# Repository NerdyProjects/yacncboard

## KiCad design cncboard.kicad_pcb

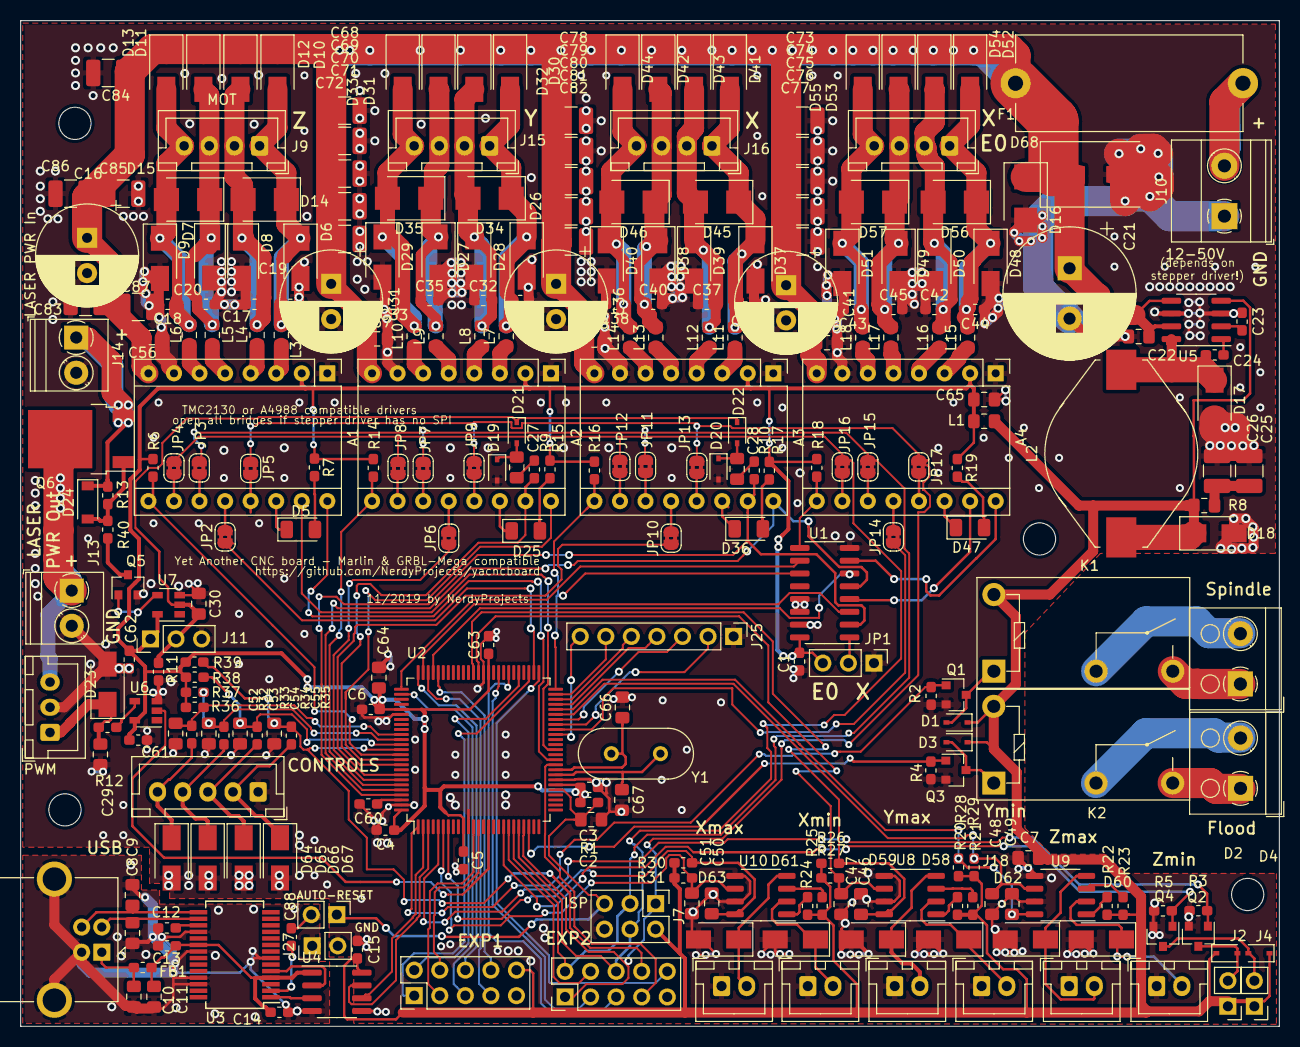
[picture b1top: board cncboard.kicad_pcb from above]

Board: 2 copper layers, 125.1 x 99.9 mm, 287 parts (0 on the bottom side), 174 nets.

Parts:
A1, A2, A3, A4: Pololu_Breakout_A4988; Pololu_Breakout-16_15.2x20.3mm
C1, C3, C4, C5, C6, C12, C13, C14, C15, C23, C24, C60, C61, C62, C63, C88: 100n; C_0603_1608Metric_Pad1.05x0.95mm_HandSolder
C2, C10: 10n; C_0805_2012Metric_Pad1.15x1.40mm_HandSolder
C7, C46, C47, C48, C49, C50, C51, C52, C53, C54, C55, C64, C65: 1µ; C_0805_2012Metric_Pad1.15x1.40mm_HandSolder
C8, C9, C66, C67: 47p; C_0805_2012Metric_Pad1.15x1.40mm_HandSolder
C11: 4u7; C_0805_2012Metric_Pad1.15x1.40mm_HandSolder
C16, C31, C36, C41: 100µF/63V; CP_Radial_D10.0mm_P3.50mm
C17, C18, C19, C20, C32, C33, C34, C35, C37, C38, C39, C40, C42, C43, C44, C45: 470p; C_0603_1608Metric_Pad1.05x0.95mm_HandSolder
C21: 470µ/63V; CP_Radial_D13.0mm_P5.00mm
C22: 1µ/50V; C_0805_2012Metric_Pad1.15x1.40mm_HandSolder
C25, C26: 22µ; C_1210_3225Metric_Pad1.42x2.65mm_HandSolder
C27, C28: 220n; C_0805_2012Metric_Pad1.15x1.40mm_HandSolder
C29: 1n; C_0805_2012Metric_Pad1.15x1.40mm_HandSolder
C30: 10µ; C_0805_2012Metric_Pad1.15x1.40mm_HandSolder
C56, C57, C58, C59: 2u2/50V; C_0805_2012Metric_Pad1.15x1.40mm_HandSolder
C68, C69, C70, C71, C72, C73, C74, C75, C76, C77, C78, C79, C80, C81, C82, C83, C84, C85, C86, C87: 10u/50V; C_1210_3225Metric_Pad1.42x2.65mm_HandSolder
D1, D2, D3, D4, D19, D20, D21, D22: 1N4148WS; D_SOD-323
D5, D25, D36, D47: LED; LED_1206_3216Metric
D6, D7, D8, D9, D10, D11, D12, D13, D17, D26, D27, D28, D29, D30, D31, D32, D33, D37, D38, D39, D40, D41, D42, D43, D44, D48, D49, D50, D51, D52, D53, D54, D55: SK36SMA; D_SMA
D14, D15, D16, D34, D35, D45, D46, D56, D57: SMBJ43CA; D_SMB
D18, D23, D58, D59, D60, D61, D62, D63, D64, D65, D66, D67: SMAJ5.0A; D_SMA
D24: MMSZ 12T1G; D_SOD-123
D68: SK36SMA; D_SMB-SMC_Universal_Handsoldering
F1: T10A; Fuseholder_Cylinder-5x20mm_Stelvio-Kontek_PTF78_Horizontal_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
FB1: BLM18PG471SN1D; L_0603_1608Metric_Pad1.05x0.95mm_HandSolder
H1, H2, H3, H4: MountingHole; MountingHole_3.2mm_M3
J1: Spindle; TerminalBlock_RND_205-00001_1x02_P5.00mm_Horizontal
J2: SPINDLE_DIRECTION; PinHeader_1x02_P2.54mm_Vertical
J3: Coolant_flood; TerminalBlock_RND_205-00001_1x02_P5.00mm_Horizontal
J4: COOLANT_MIST; PinHeader_1x02_P2.54mm_Vertical
J5: EXP1; PinHeader_2x05_P2.54mm_Vertical
J6: EXP2; PinHeader_2x05_P2.54mm_Vertical
J7: ISP; PinHeader_2x03_P2.54mm_Vertical
J8: USB_B; USB_B_OST_USB-B1HSxx_Horizontal
J9, J15, J16, J17: MOT; JST_XH_B4B-XH-A_1x04_P2.50mm_Vertical
J10: 12-45V; TerminalBlock_Phoenix_MKDS-1,5-2_1x02_P5.00mm_Horizontal
J11: Laser on/off/auto; PinHeader_1x03_P2.54mm_Vertical
J12: LASER_3PIN; JST_XH_B3B-XH-A_1x03_P2.50mm_Vertical
J13: Laser_Out; TerminalBlock_Phoenix_PT-1,5-2-3.5-H_1x02_P3.50mm_Horizontal
J14: Laser_Vcc; TerminalBlock_Phoenix_PT-1,5-2-3.5-H_1x02_P3.50mm_Horizontal
J18: Y_MIN; JST_XH_B2B-XH-A_1x02_P2.50mm_Vertical
J19: Y_MAX; JST_XH_B2B-XH-A_1x02_P2.50mm_Vertical
J20: Z_MIN; JST_XH_B2B-XH-A_1x02_P2.50mm_Vertical
J21: Z_MAX; JST_XH_B2B-XH-A_1x02_P2.50mm_Vertical
J22: X_MIN; JST_XH_B2B-XH-A_1x02_P2.50mm_Vertical
J23: X_MAX; JST_XH_B2B-XH-A_1x02_P2.50mm_Vertical
J24: Controls; JST_XH_B5B-XH-A_1x05_P2.50mm_Vertical
J25: Conn_01x07; PinHeader_1x07_P2.54mm_Vertical
J26: AUTORESET; PinHeader_1x02_P2.54mm_Vertical
J27: GND_BRIDGE; PinHeader_1x02_P2.54mm_Vertical
JP1: SolderJumper_3_Open; PinHeader_1x03_P2.54mm_Vertical
JP2, JP6, JP10, JP14: MS3; SolderJumper-2_P1.3mm_Bridged2Bar_RoundedPad1.0x1.5mm
JP3, JP7, JP11, JP15: MS2; SolderJumper-2_P1.3mm_Bridged2Bar_RoundedPad1.0x1.5mm
JP4, JP5, JP8, JP9, JP12, JP13, JP16, JP17: MS1; SolderJumper-2_P1.3mm_Bridged2Bar_RoundedPad1.0x1.5mm
K1, K2: G5Q1AEU5DC; Relay_SPST_Omron-G5Q-1A
L1: BLM18PG471SN1D; L_0805_2012Metric_Pad1.15x1.40mm_HandSolder
L2: 100µ; L_Fastron_PISR_Handsoldering
L3, L4, L5, L6, L7, L8, L9, L10, L11, L12, L13, L14, L15, L16, L17, L18: BLM21PG600; L_0805_2012Metric_Pad1.15x1.40mm_HandSolder
Q1, Q2, Q3, Q4: AO3400; SOT-23
Q5: BSS138; SOT-23
Q6: AOD409; TO-252-2
R1, R2, R3, R4, R5, R6, R14, R16, R18, R26, R27, R28, R29, R30, R31, R36, R37, R38, R39: 10k; R_0603_1608Metric_Pad1.05x0.95mm_HandSolder
R7, R11, R15, R17, R19: 1k; R_0603_1608Metric_Pad1.05x0.95mm_HandSolder
R8: 0.1; R_0805_2012Metric_Pad1.15x1.40mm_HandSolder
R9, R10, R20, R21, R22, R23, R24, R25, R32, R33, R34, R35: 470; R_0603_1608Metric_Pad1.05x0.95mm_HandSolder
R12: 100; R_0603_1608Metric_Pad1.05x0.95mm_HandSolder
R13: 100k; R_0603_1608Metric_Pad1.05x0.95mm_HandSolder
R40: 4k7; R_0603_1608Metric_Pad1.05x0.95mm_HandSolder
U1: 74LS157; SOIC-16_3.9x9.9mm_P1.27mm
U2: ATmega2560-16AU; TQFP-100_14x14mm_P0.5mm
U3: FT232RL; SSOP-28_5.3x10.2mm_P0.65mm
U4: ADuM1201AR; SOIC-8_3.9x4.9mm_P1.27mm
U5: MAX5035BUSA; SOIC-8_3.9x4.9mm_P1.27mm
U6, U7: 74AUC1G17; SOT-23-5
U8, U9, U10: LTV-827S; SO-8_3.9x4.9mm_P1.27mm
Y1: LFXTAL003240l; Crystal_HC49-4H_Vertical

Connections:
+5V: C7.1, C15.1, D1.1, D2.1, D3.1, D4.1, D18.1, J2.1, J4.1, J5.10, J7.2, K1.5, K2.5, L1.1, L2.2, R8.1, R20.2, R21.2, R22.2, R23.2, R24.2, R25.2, R26.2, R27.2, R28.2, R29.2, R30.2, R31.2, U4.8, U5.4
+5VD: A1.2, A2.2, A3.2, A4.2, C1.1, C3.1, C4.1, C5.1, C6.1, C61.2, C62.2, C63.1, C64.1, C65.1, J11.1, JP1.3, L1.2, R1.1, R6.1, R7.1, R14.1, R15.1, R16.1, R17.1, R18.1, R19.1, R36.2, R37.2, R38.2, R39.2, U1.16, U2.10, U2.31, U2.61, U2.80, U2.100, U6.5, U7.5
+VDC: A1.8, A2.8, A3.8, A4.8, C16.1, C21.1, C22.1, C31.1, C36.1, C41.1, C56.1, C57.1, C58.1, C59.1, C68.1, C69.1, C70.1, C71.1, C72.1, C73.1, C74.1, C75.1, C76.1, C77.1, C78.1, C79.1, C80.1, C81.1, C82.1, C83.1, C84.1, C85.1, C86.1, C87.1, D10.1, D11.1, D12.1, D13.1, D16.1, D30.1, D31.1, D32.1, D33.1, D41.1, D42.1, D43.1, D44.1, D52.1, D53.1, D54.1, D55.1, D68.1, F1.2, U5.5, U5.7
/Stepper E0/CS: JP14.1, U2.42
/Stepper E0/DCO: A4.14, D47.1
/Stepper E0/DIR: A4.16, U1.7
/Stepper E0/EN: A4.9, R18.2, U1.9
/Stepper E0/SCK: J6.2, J7.3, JP3.1, JP7.1, JP11.1, JP15.1, U2.20
/Stepper E0/STEP: A4.15, U1.4
/Stepper X/CS: JP10.1, U2.93
/Stepper X/DCO: A3.14, D36.1
/Stepper X/DIR: A3.16, U1.5, U2.96
/Stepper X/EN: A3.9, R16.2, U1.11, U2.50
/Stepper X/STEP: A3.15, R10.2, U1.2, U2.97
/Stepper Y/CS: JP6.1, U2.94
/Stepper Y/DCO: A2.14, D25.1
/Stepper Y/DIR: A2.16, U2.90
/Stepper Y/EN: A2.9, R14.2, U2.95
/Stepper Y/STEP: A2.15, R9.2, U2.91
/Stepper Z/CS: JP2.1, U2.52
/Stepper Z/DCO: A1.14, D5.1
/Stepper Z/DIR: A1.16, U2.36
/Stepper Z/EN: A1.9, R6.2, U2.89
/Stepper Z/STEP: A1.15, U2.38
/inputs/CYCLE_START: C53.1, R33.1, R37.1, U2.86
/inputs/FEED_HOLD: C54.1, R34.1, R38.1, U2.87
/inputs/SAFETY_DOOR: C52.1, R32.1, R36.1, U2.85
/inputs/SOFT_RESET: C55.2, J6.8, R35.1, R39.1, U2.88
/inputs/X_MAX: C51.1, R31.1, U2.6, U10.6
/inputs/X_MIN: C50.1, R30.1, U2.7, U10.8
/inputs/Y_MAX: C47.1, R27.1, U2.63, U8.6
/inputs/Y_MIN: C46.1, R26.1, U2.64, U8.8
/inputs/Z_MAX: C49.1, R29.1, U2.45, U9.6
/inputs/Z_MIN: C48.1, R28.1, U2.46, U9.8
/laser/LASER_VCC: J12.3, J13.1, Q6.2
/mcu/COOLANT_FLOOD: Q3.1, R4.1, U2.23
/mcu/COOLANT_MIST: Q4.1, R5.1, U2.18
/mcu/DIR_E0: U1.6, U2.72
/mcu/EN_E0: U1.10, U2.76
/mcu/LASER_PWM: U2.15, U6.2
/mcu/MISO: J6.1, J7.1, JP5.1, JP9.1, JP13.1, JP17.1, U2.22
/mcu/MOSI: J6.6, J7.4, JP4.1, JP8.1, JP12.1, JP16.1, U2.21
/mcu/PA1: J5.5, U2.77
/mcu/PA3: J5.6, U2.75
/mcu/PA5: J5.7, U2.73
/mcu/PA7: J5.8, U2.71
/mcu/PB0: J6.4, U2.19
/mcu/PC0: J5.1, U2.53
/mcu/PC2: J5.2, U2.55
/mcu/PC4: J6.5, U2.57
/mcu/PC6: J6.3, U2.59
/mcu/PG0: J6.10, U2.51
/mcu/PH0: J5.3, U2.12
/mcu/PH1: J5.4, U2.13
/mcu/PL0: J6.7, U2.35
/mcu/PL6: J25.7, U2.41
/mcu/RESET: C2.1, J7.5, J26.1, R1.2, U2.30
/mcu/RX: U2.2, U4.6
/mcu/SPINDLE_DIRECTION: Q2.1, R3.1, U2.5
/mcu/SPINDLE_ENABLE: Q1.1, R2.1, U2.1
/mcu/STEP_E0: U1.3, U2.74
/usb/DTR: C88.2, U3.2
/usb/RX: U2.3, U4.7
GND: A1.1, A1.7, A2.1, A2.7, A3.1, A3.7, A4.1, A4.7, C1.2, C2.2, C3.2, C4.2, C5.2, C6.2, C7.2, C15.2, C16.2, C17.1, C18.2, C19.1, C20.2, C21.2, C22.2, C23.2, C25.2, C26.2, C29.1, C30.1, C31.2, C32.1, C33.2, C34.1, C35.2, C36.2, C37.1, C38.2, C39.1, C40.2, C41.2, C42.1, C43.2, C44.1, C45.2, C46.2, C47.2, C48.2, C49.2, C50.2, C51.2, C52.2, C53.2, C54.2, C55.1, C56.2, C57.2, C58.2, C59.2, C60.2, C61.1, C62.1, C63.2, C64.2, C65.2, C66.2, C67.2, C68.2, C69.2, C70.2, C71.2, C72.2, C73.2, C74.2, C75.2, C76.2, C77.2, C78.2, C79.2, C80.2, C81.2, C82.2, C83.2, C84.2, C85.2, C86.2, C87.2, D6.2, D7.2, D8.2, D9.2, D16.2, D17.2, D18.2, D19.2, D20.2, D23.2, D26.2, D27.2, D28.2, D29.2, D37.2, D38.2, D39.2, D40.2, D48.2, D49.2, D50.2, D51.2, D58.2, D59.2, D60.2, D61.2, D62.2, D63.2, D64.2, D65.2, D66.2, D67.2, D68.2, J5.9, J6.9, J7.6, J10.1, J11.3, J12.2, J13.2, J14.2, J18.1, J19.1, J20.1, J21.1, J22.1, J23.1, J24.1, J25.1, J27.2, JP1.1, Q1.2, Q2.2, Q3.2, Q4.2, Q5.2, R2.2, R3.2, R4.2, R5.2, R11.1, U1.8, U1.13, U1.14, U1.15, U2.11, U2.32, U2.62, U2.81, U2.99, U4.5, U5.3, U5.6, U6.3, U7.3, U8.5, U8.7, U9.5, U9.7, U10.5, U10.7
unnamed: A1.3, L3.1
unnamed: A1.4, L4.1
unnamed: A1.5, L5.1
unnamed: A1.6, L6.1
unnamed: A1.10, JP4.2
unnamed: A1.11, JP3.2
unnamed: A1.12, JP2.2
unnamed: A1.13, JP5.2
unnamed: A2.3, L7.1
unnamed: A2.4, L8.1
unnamed: A2.5, L9.1
unnamed: A2.6, L10.1
unnamed: A2.10, JP8.2
unnamed: A2.11, JP7.2
unnamed: A2.12, JP6.2
unnamed: A2.13, JP9.2
unnamed: A3.3, L11.1
unnamed: A3.4, L12.1
unnamed: A3.5, L13.1
unnamed: A3.6, L14.1
unnamed: A3.10, JP12.2
unnamed: A3.11, JP11.2
unnamed: A3.12, JP10.2
unnamed: A3.13, JP13.2
unnamed: A4.3, L15.1
unnamed: A4.4, L16.1
unnamed: A4.5, L17.1
unnamed: A4.6, L18.1
unnamed: A4.10, JP16.2
unnamed: A4.11, JP15.2
unnamed: A4.12, JP14.2
unnamed: A4.13, JP17.2
unnamed: C8.1, J8.2, U3.16
unnamed: C9.1, J8.3, U3.15
unnamed: C10.1, FB1.2, J8.1
unnamed: C8.2, C9.2, C10.2, C11.2, C12.2, C13.2, C14.2, J8.4, J8.5, J27.1, U3.7, U3.18, U3.21, U3.25, U3.26, U4.4
unnamed: C11.1, C13.1, C14.1, FB1.1, U3.4, U3.20, U4.1
unnamed: C12.1, U3.17
unnamed: C17.2, D8.1, D12.2, D14.2, J9.2, L4.2
unnamed: C18.1, D9.1, D13.2, D15.2, J9.4, L6.2
unnamed: C19.2, D6.1, D10.2, D14.1, J9.1, L3.2
unnamed: C20.1, D7.1, D11.2, D15.1, J9.3, L5.2
unnamed: C23.1, U5.2
unnamed: C24.1, U5.1
unnamed: C24.2, D17.1, L2.1, U5.8
unnamed: C25.1, C26.1, R8.2
unnamed: C27.1, D19.1, D21.2
unnamed: C27.2, R9.1
unnamed: C28.1, D20.1, D22.2
unnamed: C28.2, R10.1
unnamed: C29.2, D23.1, J12.1, R12.1
unnamed: C30.2, D21.1, D22.1, J11.2, R11.2, U7.2
unnamed: C32.2, D28.1, D32.2, D34.2, J15.2, L8.2
unnamed: C33.1, D29.1, D33.2, D35.2, J15.4, L10.2
unnamed: C34.2, D26.1, D30.2, D34.1, J15.1, L7.2
unnamed: C35.1, D27.1, D31.2, D35.1, J15.3, L9.2
unnamed: C37.2, D39.1, D43.2, D45.2, J16.2, L12.2
unnamed: C38.1, D40.1, D44.2, D46.2, J16.4, L14.2
unnamed: C39.2, D37.1, D41.2, D45.1, J16.1, L11.2
unnamed: C40.1, D38.1, D42.2, D46.1, J16.3, L13.2
unnamed: C42.2, D50.1, D54.2, D56.2, J17.2, L16.2
unnamed: C43.1, D51.1, D55.2, D57.2, J17.4, L18.2
unnamed: C44.2, D48.1, D52.2, D56.1, J17.1, L15.2
unnamed: C45.1, D49.1, D53.2, D57.1, J17.3, L17.2
unnamed: C60.1, U2.98
unnamed: C66.1, U2.34, Y1.1
unnamed: C67.1, U2.33, Y1.2
unnamed: C88.1, J26.2
unnamed: D1.2, K1.1, Q1.3
unnamed: D2.2, J2.2, Q2.3
unnamed: D3.2, K2.1, Q3.3
unnamed: D4.2, J4.2, Q4.3
unnamed: D5.2, R7.2
unnamed: D24.1, J14.1, Q6.3, R13.2
unnamed: D24.2, Q6.1, R13.1, R40.2
unnamed: D25.2, R15.2
unnamed: D36.2, R17.2
unnamed: D47.2, R19.2
unnamed: D58.1, J18.2, U8.2
unnamed: D59.1, J19.2, U8.4
unnamed: D60.1, J20.2, U9.2
unnamed: D61.1, J22.2, U10.2
unnamed: D62.1, J21.2, U9.4
unnamed: D63.1, J23.2, U10.4
unnamed: D64.1, J24.5, R32.2
unnamed: D65.1, J24.4, R33.2
unnamed: D66.1, J24.3, R34.2
unnamed: D67.1, J24.2, R35.2
unnamed: F1.1, J10.2
unnamed: J1.1, K1.3
unnamed: J1.2, K1.2
unnamed: J3.1, K2.3
unnamed: J3.2, K2.2
unnamed: J25.2, U2.43
unnamed: J25.3, U2.44
unnamed: J25.4, U2.47
unnamed: J25.5, U2.48
unnamed: J25.6, U2.49
unnamed: JP1.2, U1.1
unnamed: Q5.1, U7.4
unnamed: Q5.3, R40.1
unnamed: R12.2, U6.4
unnamed: R20.1, U8.1
unnamed: R21.1, U8.3
unnamed: R22.1, U9.1
unnamed: R23.1, U9.3
unnamed: R24.1, U10.1
unnamed: R25.1, U10.3
unnamed: U3.1, U4.3
unnamed: U3.5, U4.2

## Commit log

2019-10-31 First routing attempt
2019-10-31 Placement update
2019-10-31 routing in progress
2019-11-02 Finish routing/nicifying V1
2019-11-02 Silk screen adjustments
2019-11-08 add autoreset and USB GND bridge
